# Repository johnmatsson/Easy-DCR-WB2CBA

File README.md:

Easy-DCR-F4JRX Poor Mans HF RX
===============================

A simple Arduino based direct conversion HF digital modes SSB receiver. 

This is a fork of WB2CBA's work from February 2020 : WB2CBA Barbaros Asuroglu.

The kit used for my developments was provided by F5KSE radio-club (http://ref31.r-e-f.org/) with the help of F4JQT (does not include the low-band filter).

The software from WB2CBA has been changed to :
1. Add support for CAT control over USB serial from WSJT-X and JS8Call
2. Rearrange DIP switch configuration to support multi-band operation

CAT Control operation
=====================

CAT Control is emulating a Yaesu FT-991.

WSJT-X and JS8Call should be configured as follows :
- Radio : Yaesu FT-991
- Baud rate : 115200
- Data bits : Default
- Stop bits : Default
- **Handshake : None** /!\ 

Configuration screen for WSJT-X :

Configuration screen for JS8Call :

DIP Switch configuration
========================
Swtich 0 and 1 are used for band selection.

Swtich 2 and 3 are used for mode selection.

Switch 0-1 = Band :
-------------------

| Switch   |  0   |   1   |
|:---------|:----:|------:|
|   80m    |  0   |   0   |
|   40m    |  0   |   1   |
|   30m    |  1   |   0   |
|   10m    |  1   |   1   |

Switch 2-3 = Mode :
-------------------

| Switch   |  2   |   3   |
|:---------|:----:|------:|
|   FT4    |  0   |   0   |
|   FT8    |  0   |   1   |
|   WSPR   |  1   |   0   |
|   JS8    |  1   |   1   |

Demonstration
=============
The board assembled and connected to the PC (USB Serial for CAT control and mic input jack for audio) and to my HWEF antenna :	

In action with WSJT-X in FT8 mode on 40m :

Assembly and build instructions
===============================
https://antrak.org.tr/projeler/poor-mans-hf-ssb-receiver-lets-build-it/

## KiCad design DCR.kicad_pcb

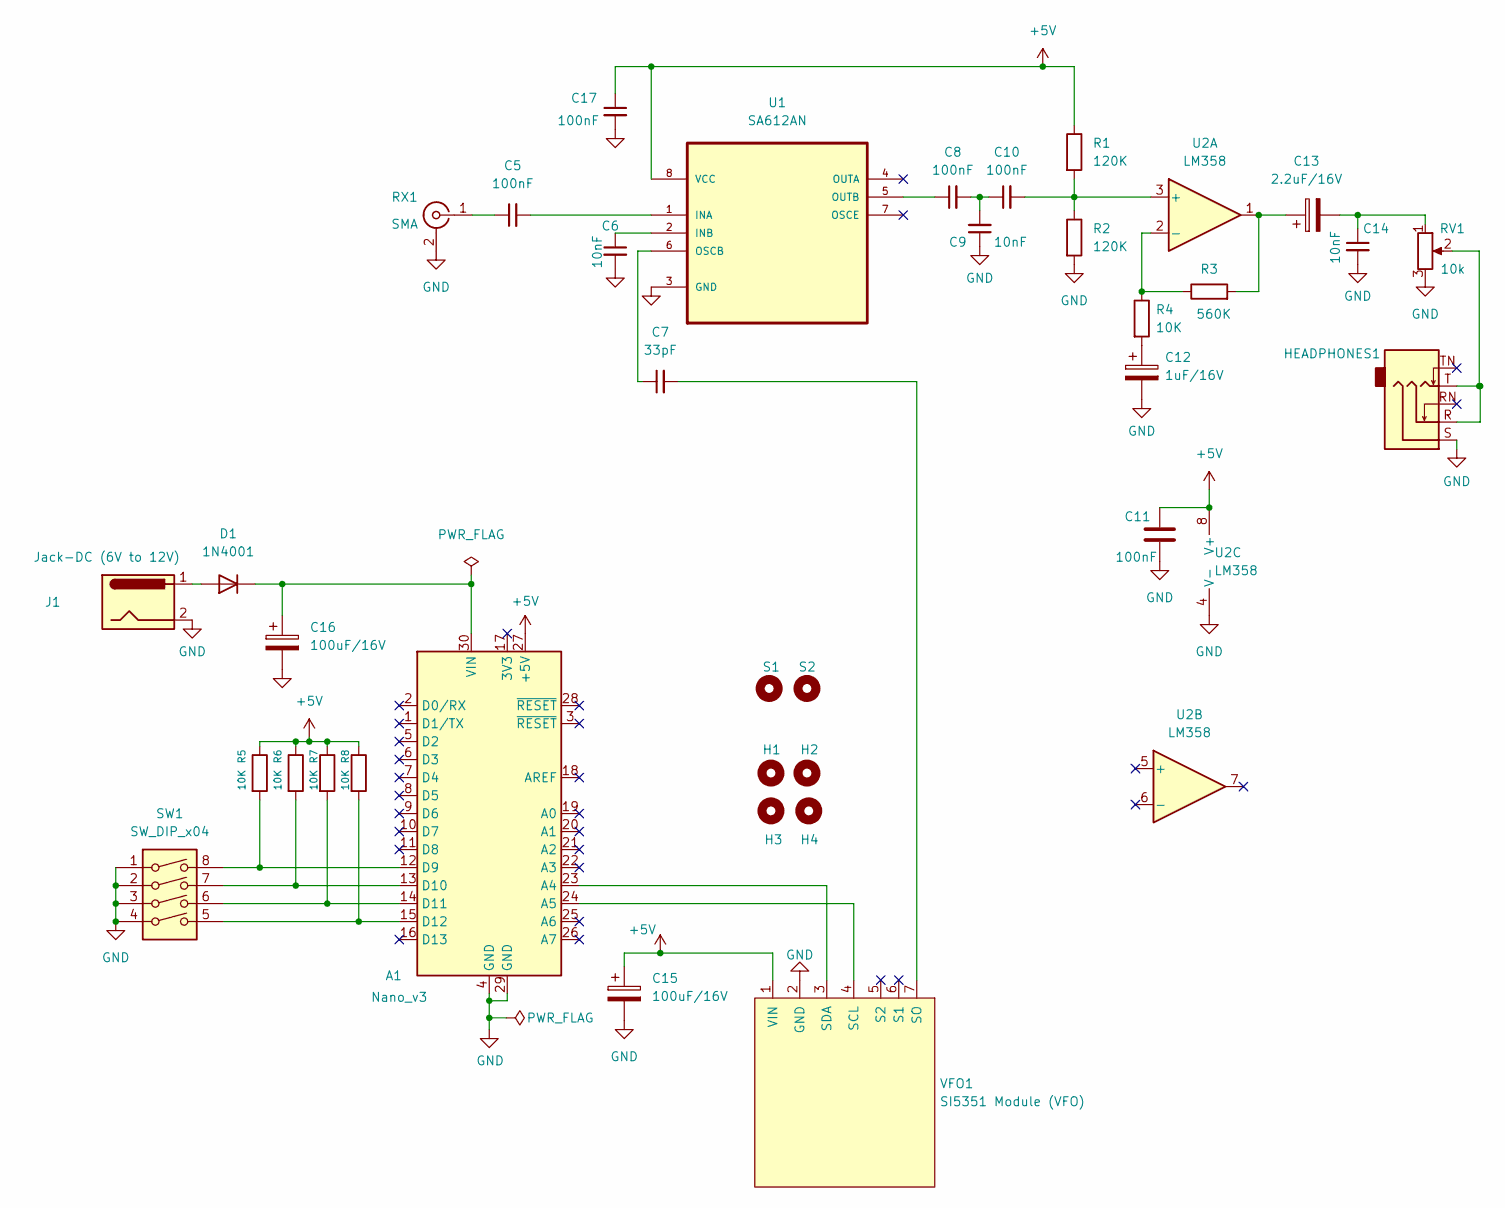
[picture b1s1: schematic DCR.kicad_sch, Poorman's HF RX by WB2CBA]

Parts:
A1: Nano_v3; Arduino_Nano
C5, C8, C10, C11, C17: 100nF; C_Disc_D3.0mm_W1.6mm_P2.50mm
C6, C9, C14: 10nF; C_Disc_D3.0mm_W1.6mm_P2.50mm
C7: 33pF; C_Disc_D3.0mm_W1.6mm_P2.50mm
C12: 1uF/16V; CP_Radial_D5.0mm_P2.00mm
C13: 2.2uF/16V; CP_Radial_D5.0mm_P2.00mm
C15, C16: 100uF/16V; CP_Radial_D5.0mm_P2.00mm
D1: 1N4001; D_DO-41_SOD81_P2.54mm_Vertical_KathodeUp
H1, H2, H3, H4: MountingHole; MountingHole_2.2mm_M2
HEADPHONES1: AudioJack3_SwitchTR; PJ-307
J1: Jack-DC (6V to 12V); PinSocket_1x02_P2.54mm_Vertical
R1: 120K; R_Axial_DIN0207_L6.3mm_D2.5mm_P7.62mm_Horizontal
R2: 120K
R3: 560K
R4, R5, R6, R7, R8: 10K
RV1: 10k; Potentiometer_Runtron_RM-065_Vertical
RX1: SMA; SMA_Amphenol_901-144_Vertical
S1, S2: MountingHole; MountingHole_2.7mm_M2.5
SW1: SW_DIP_x04; SW_DIP_SPSTx04_Slide_9.78x12.34mm_W7.62mm_P2.54mm
U1: SA612AN; DIP-8_W7.62mm; MPN SA602AN
U2: LM358; DIP-8_W7.62mm
VFO1: SI5351 Module (VFO); PinSocket_1x07_P2.54mm_Vertical

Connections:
+5V: A1.27 (+5V), C11.1, C15.1, C17.1, R1.1, R5.1, R6.1, R7.1, R8.1, U1.8 (VCC), U2.8 (V+), VFO1.1 (VIN)
GND: A1.4 (GND), A1.29 (GND), C6.2, C9.1, C11.2, C12.2, C14.2, C15.2, C16.2, C17.2, HEADPHONES1.S, J1.2, R2.2, RV1.3, RX1.2 (Ext), SW1.1, SW1.2, SW1.3, SW1.4, U1.3 (GND), U2.4 (V-), VFO1.2 (GND)
unnamed: A1.12 (D9), R5.2, SW1.8
unnamed: A1.13 (D10), R6.2, SW1.7
unnamed: A1.14 (D11), R7.2, SW1.6
unnamed: A1.15 (D12), R8.2, SW1.5
unnamed: A1.23 (A4), VFO1.3 (SDA)
unnamed: A1.24 (A5), VFO1.4 (SCL)
unnamed: A1.30 (VIN), C16.1, D1.1 (K)
unnamed: C5.1, RX1.1 (In)
unnamed: C5.2, U1.1 (INA)
unnamed: C6.1, U1.2 (INB)
unnamed: C7.1, U1.6 (OSCB)
unnamed: C7.2, VFO1.7 (SO)
unnamed: C8.1, U1.5 (OUTB)
unnamed: C8.2, C9.2, C10.1
unnamed: C10.2, R1.2, R2.1, U2.3 (+)
unnamed: C12.1, R4.2
unnamed: C13.1, R3.2, U2.1
unnamed: C13.2, C14.1, RV1.1
unnamed: D1.2 (A), J1.1
unnamed: HEADPHONES1.R, HEADPHONES1.T, RV1.2
unnamed: R3.1, R4.1, U2.2 (-)

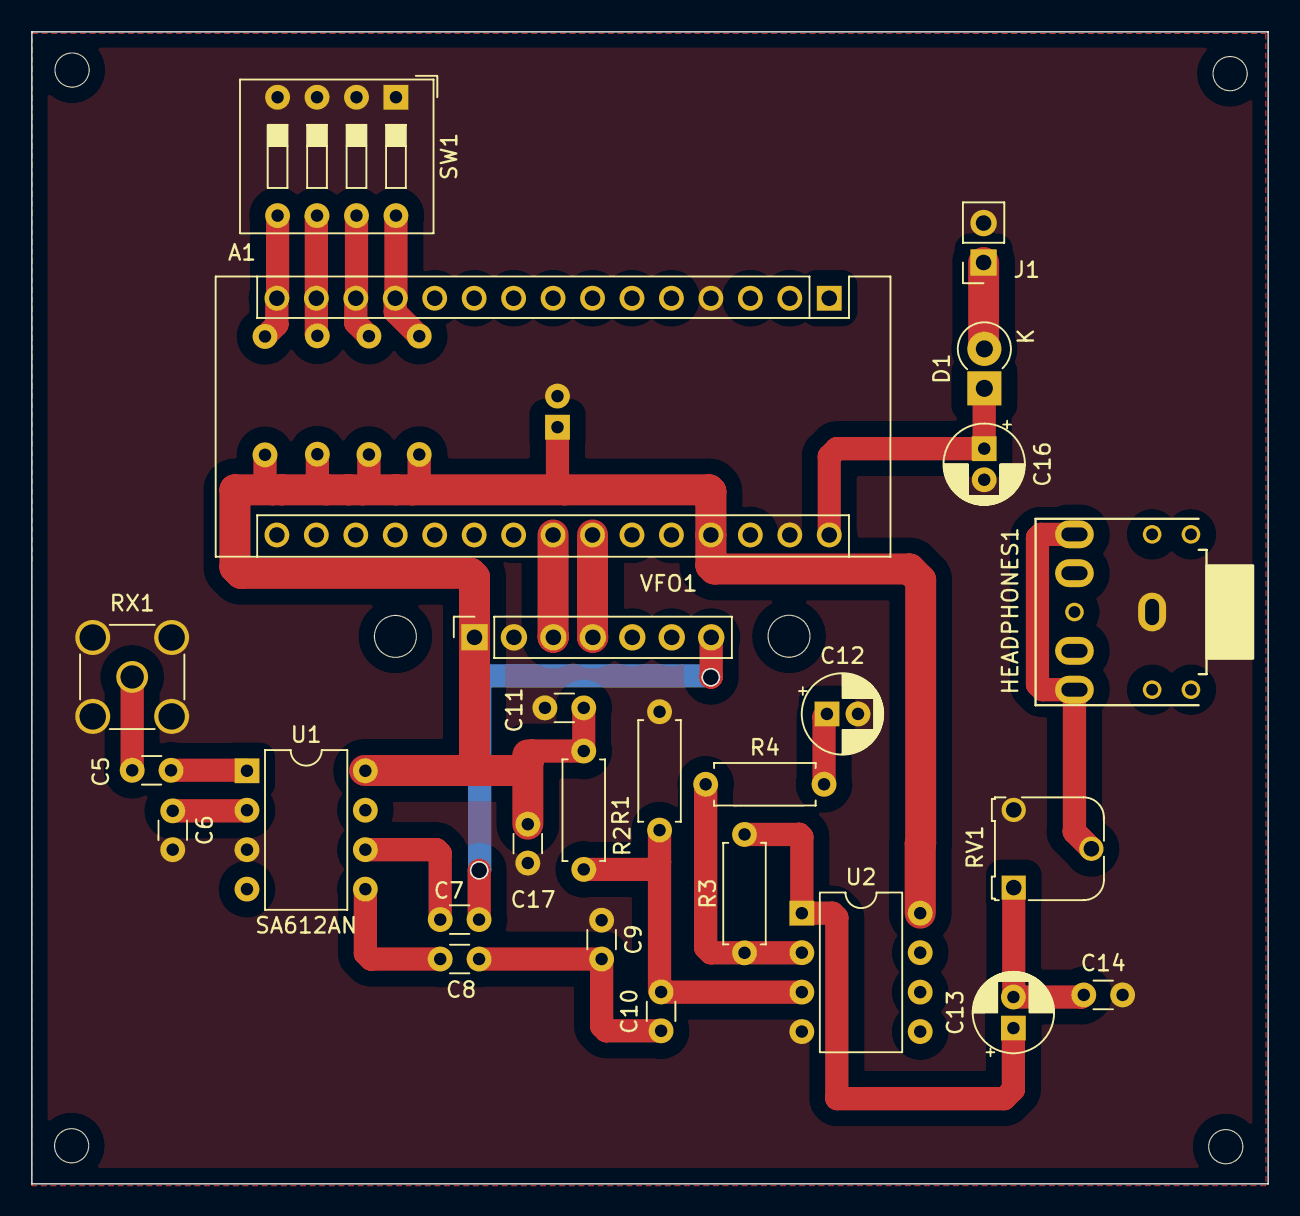
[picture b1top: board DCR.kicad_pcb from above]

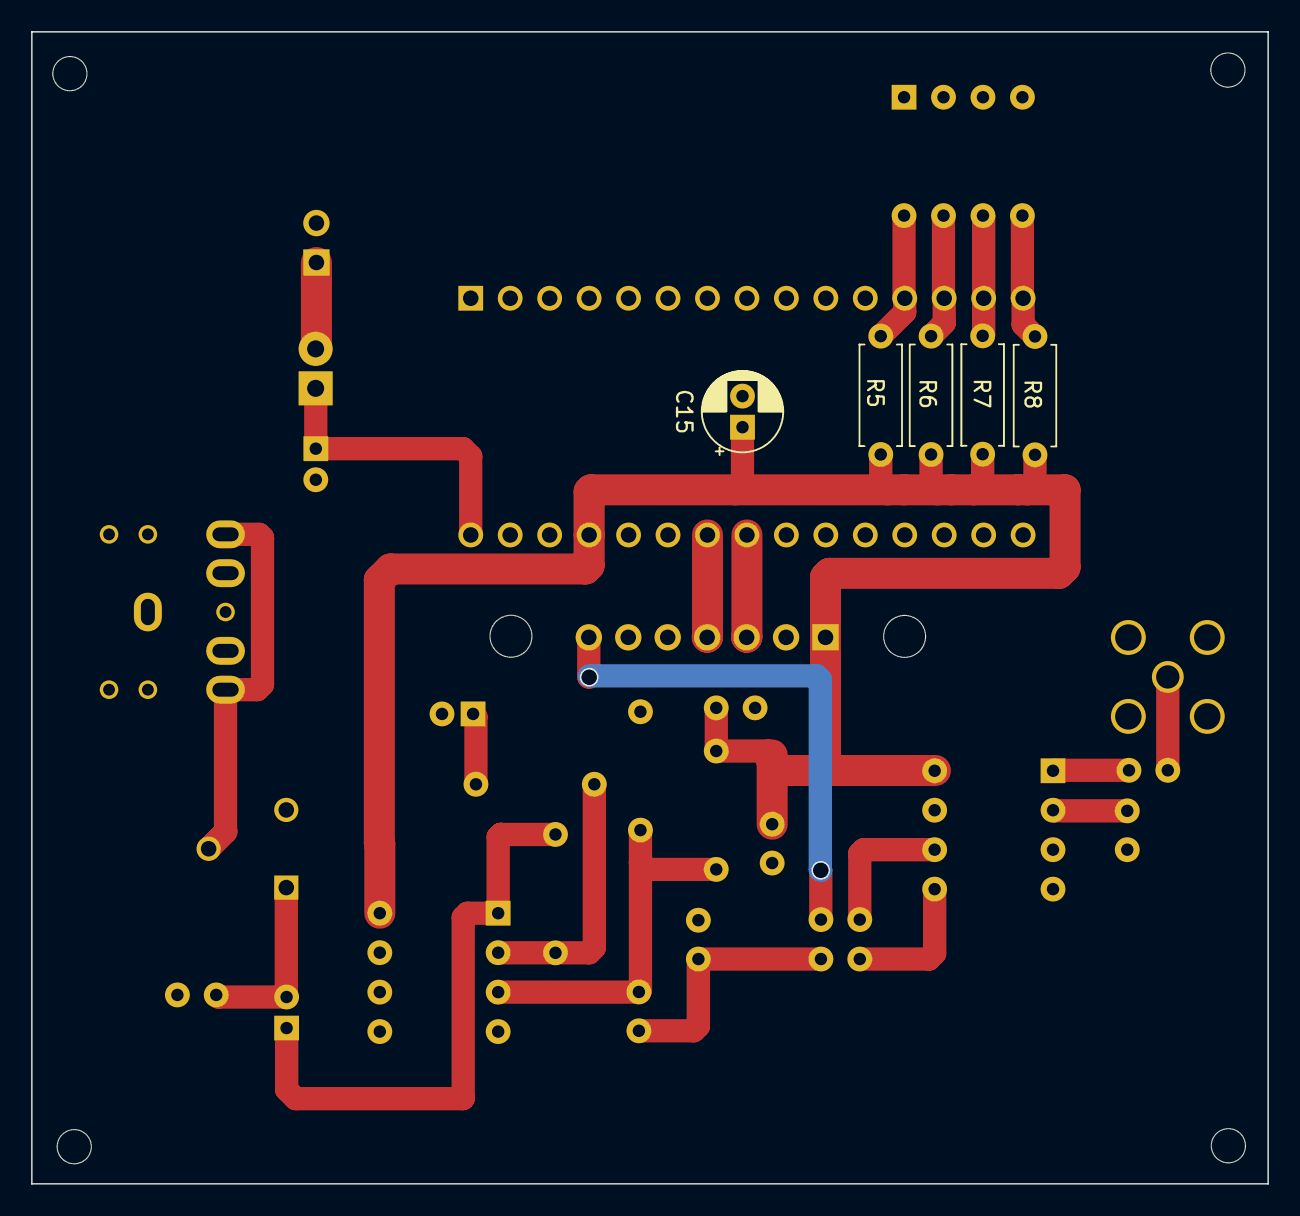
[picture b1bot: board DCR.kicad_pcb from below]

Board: 2 copper layers, 79.6 x 74.2 mm, 37 parts (5 on the bottom side), 23 nets.

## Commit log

2023-07-24 Initial commit.
2023-07-24 Added readme.
2023-07-24 Fixed typos
2023-07-24 Added demo section
2023-07-24 Typo
2023-07-24 Fixed bold
2023-07-24 Table formatting
